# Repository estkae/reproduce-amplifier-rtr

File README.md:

# Reproduce amplifier for reel to reel tape recorders

Mainly built for Soviet-era tape recorders using heads: 6В24.080 and similar. Main emphasis is made on accuracy of the reproduction, targeting both precise and noise free reproduction. For this reason it is using ultra low noise AD8429 instrumentation amplifiers and has very careful ground layout. 

It wasn't tested with other speeds than 19 cm/s speed.

Dedicated to my father Vladimir Sibiryakov.

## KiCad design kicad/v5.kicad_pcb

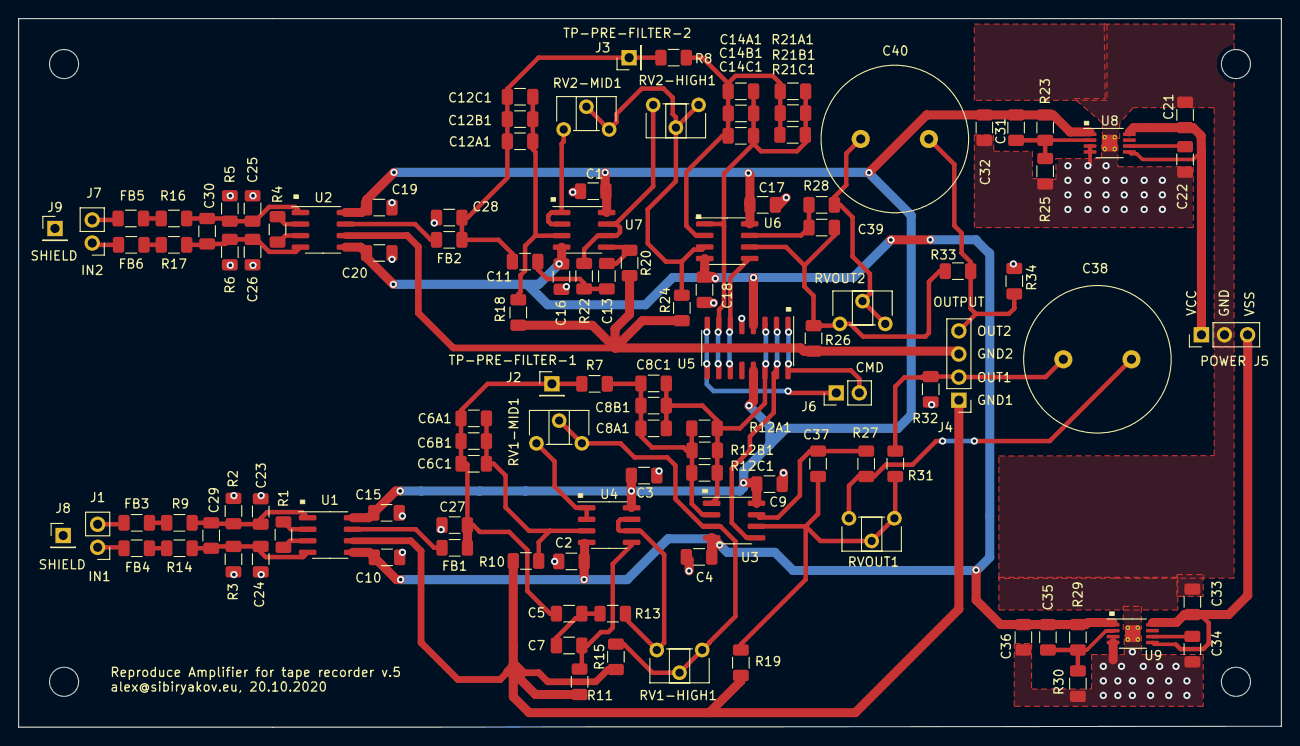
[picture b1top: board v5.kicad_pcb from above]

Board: 2 copper layers, 139.0 x 78.0 mm, 116 parts (0 on the bottom side), 57 nets.

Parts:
C1, C2, C3, C4, C9, C10, C15, C16, C17, C18, C19, C20, C27, C28: 0.1uF; C_1206_3216Metric
C5, C7: 6.8n, 1%; C_1206_3216Metric
C6A1, C6B1, C8A1, C8B1, C12A1, C12B1, C14A1, C14B1: 39n, 1%; C_1206_3216Metric
C6C1, C12C1: 22n, 1%; C_1206_3216Metric
C8C1, C14C1: 82n, 1%; C_1206_3216Metric
C11, C13: 6.8n; C_1206_3216Metric
C21, C32, C33, C36: 10u; C_1206_3216Metric
C22, C31, C34, C35: 10n; C_1206_3216Metric
C23, C24, C25, C26: 47p; C_1206_3216Metric
C29, C30: 10nF; C_1206_3216Metric
C37, C39: 100pF; C_1206_3216Metric
C38, C40: 100U 35V NP; C_Radial_D16.0mm_H25.0mm_P7.50mm
FB1, FB2: Ferrite_Bead; L_1206_3216Metric
FB3, FB4, FB5, FB6: Ferrite_Bead_Small; L_1206_3216Metric
J1: IN1; PinHeader_1x02_P2.54mm_Vertical
J2: TP-PRE-FILTER-1; PinHeader_1x01_P2.54mm_Vertical
J3: TP-PRE-FILTER-2; PinHeader_1x01_P2.54mm_Vertical
J4: Output; PinHeader_1x04_P2.54mm_Vertical
J5: Power; PinHeader_1x03_P2.54mm_Vertical
J6: CMD; PinHeader_1x02_P2.54mm_Vertical
J7: IN2; PinHeader_1x02_P2.54mm_Vertical
J8: SHIELD1; PinHeader_1x01_P2.54mm_Vertical
J9: SHIELD2; PinHeader_1x01_P2.54mm_Vertical
R1, R4: 12.1; R_1206_3216Metric
R2, R3, R5, R6: 22k; R_1206_3216Metric
R7, R8: 5.6k; R_1206_3216Metric
R9, R14, R16, R17: 33; R_1206_3216Metric
R10: 1.5k, 1%; R_1206_3216Metric
R11, R20: 1.25k; R_1206_3216Metric
R12A1, R21A1: 18k, 1%; R_1206_3216Metric
R12B1, R21B1: 39k, 1%; R_1206_3216Metric
R12C1, R21C1: 51k, 1%; R_1206_3216Metric
R13, R22: 625; R_1206_3216Metric
R15, R24: 3.9k; R_1206_3216Metric
R18: 1.5k; R_1206_3216Metric
R19, R26: 560; R_1206_3216Metric
R23, R29: 91k; R_1206_3216Metric
R25, R30: 10k; R_1206_3216Metric
R27, R28: 68; R_1206_3216Metric
R31, R33: 1K; R_1206_3216Metric
R32, R34: 22K; R_1206_3216Metric
RV1-HIGH1, RV1-MID1, RV2-MID1: 3k; Potentiometer_Piher_PT-6-H_Horizontal
RV2-HIGH1: 3K; Potentiometer_Piher_PT-6-H_Horizontal
RVOUT1, RVOUT2: 7.5k; Potentiometer_Piher_PT-6-H_Horizontal
U1, U2: AD8429; SOIC-8_3.9x4.9mm_P1.27mm
U3, U4, U6, U7: NE5532; SOIC-8_3.9x4.9mm_P1.27mm
U5: ADG442; SOIC-16_3.9x9.9mm_P1.27mm
U8: TPS7A49; MSOP-8-1EP_3x3mm_P0.65mm_EP1.73x1.85mm_ThermalVias
U9: TPS7A30xx; MSOP-8-1EP_3x3mm_P0.65mm_EP1.73x1.85mm_ThermalVias

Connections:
GND: C1.2, C2.2, C3.2, C4.2, C9.1, C10.1, C15.1, C16.1, C17.1, C18.1, C19.1, C20.1, C21.2, C22.1, C23.2, C24.2, C25.2, C26.2, C27.2, C28.2, C32.1, C33.2, C34.1, C36.1, J4.1, J4.3, J5.2, J8.1, J9.1, R2.2, R3.2, R5.2, R6.2, R10.2, R11.2, R15.1, R18.2, R19.2, R20.2, R24.1, R25.1, R26.2, R30.1, R32.2, R34.2, U1.6, U2.6, U5.5, U8.3, U8.4, U8.9, U9.3, U9.4, U9.9
unnamed: C5.1, C7.2, R13.2
unnamed: C6A1.1, C6B1.1, C6C1.1, R10.1, U4.3
unnamed: C7.1, R11.1, U4.5
unnamed: C8A1.1, C8B1.1, C8C1.1, R12A1.1, R12B1.1, R12C1.1, U3.1, U5.3, U5.14
unnamed: C8A1.2, C8B1.2, C8C1.2, R7.1, R12A1.2, R12B1.2, R12C1.2, U3.2
unnamed: C11.1, C13.2, R22.2
unnamed: C11.2, C12A1.2, C12B1.2, C12C1.2, C28.1, FB2.1, J3.1, R8.2
unnamed: C12A1.1, C12B1.1, C12C1.1, R18.1, U7.3
unnamed: C13.1, R20.1, U7.5
unnamed: C14A1.1, C14B1.1, C14C1.1, R21A1.1, R21B1.1, R21C1.1, U5.7, U5.10, U6.1
unnamed: C14A1.2, C14B1.2, C14C1.2, R8.1, R21A1.2, R21B1.2, R21C1.2, U6.2
unnamed: C21.1, J5.1, U8.5, U8.8
unnamed: C22.2, U8.6
unnamed: C23.1, C29.1, R2.1, R9.1, U1.1
unnamed: C24.1, C29.2, R3.1, R14.1, U1.4
unnamed: C25.1, C30.1, R5.1, R16.1, U2.1
unnamed: C26.1, C30.2, R6.1, R17.1, U2.4
unnamed: C5.2, C6A1.2, C6B1.2, C6C1.2, C27.1, FB1.1, J2.1, R7.2
unnamed: C31.1, R23.1, R25.2, U8.2
unnamed: C33.1, J5.3, U9.5, U9.8
unnamed: C34.2, U9.6
unnamed: C35.1, R29.1, R30.2, U9.2
unnamed: C37.1, R27.2, U3.7
unnamed: C37.2, R19.1, R31.2, RVOUT1.1, RVOUT1.2, U3.6
unnamed: C38.1, J4.2, R31.1, R32.1
unnamed: C38.2, R27.1, RVOUT1.3
unnamed: C39.1, R28.1, U6.7
unnamed: C39.2, R26.1, R33.2, RVOUT2.1, U6.6
unnamed: C40.1, J4.4, R33.1, R34.1
unnamed: C40.2, R28.2, RVOUT2.2, RVOUT2.3
unnamed: FB1.2, U1.7
unnamed: FB2.2, U2.7
unnamed: FB3.1, R9.2
unnamed: FB3.2, J1.2
unnamed: FB4.1, R14.2
unnamed: FB4.2, J1.1
unnamed: FB5.1, R16.2
unnamed: FB5.2, J7.2
unnamed: FB6.1, R17.2
unnamed: FB6.2, J7.1
unnamed: J6.1, U5.8, U5.9
unnamed: J6.2, U5.1, U5.16
unnamed: R1.1, U1.2
unnamed: R1.2, U1.3
unnamed: R4.1, U2.2
unnamed: R4.2, U2.3
unnamed: R13.1, RV1-HIGH1.3, U4.6, U4.7
unnamed: R15.2, RV1-HIGH1.1, RV1-HIGH1.2, RV1-MID1.2, RV1-MID1.3, U3.3
unnamed: R22.1, RV2-HIGH1.3, U7.6, U7.7
unnamed: R24.2, RV2-HIGH1.1, RV2-HIGH1.2, RV2-MID1.2, RV2-MID1.3, U6.3
unnamed: RV1-MID1.1, U4.1, U4.2
unnamed: RV2-MID1.1, U7.1, U7.2
unnamed: U3.5, U5.2, U5.15
unnamed: U5.6, U5.11, U6.5
VCC: C1.1, C3.1, C9.2, C15.2, C17.2, C19.2, C31.2, C32.2, R23.2, U1.8, U2.8, U3.8, U4.8, U5.13, U6.8, U7.8, U8.1
VSS: C2.1, C4.1, C10.2, C16.2, C18.2, C20.2, C35.2, C36.2, R29.2, U1.5, U2.5, U3.4, U4.4, U5.4, U6.4, U7.4, U9.1

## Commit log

2020-10-21 kicad and ltspice files
2020-10-21 Output stage PCB work
2020-10-21 WIP Capacitors from E12, and resistors from E24/12
2020-10-23 measurements, graphs
2020-10-25 E24 canges on PCB
2020-11-01 More work on putting filter capacitors, Proper net assignment on power regulators grounds
